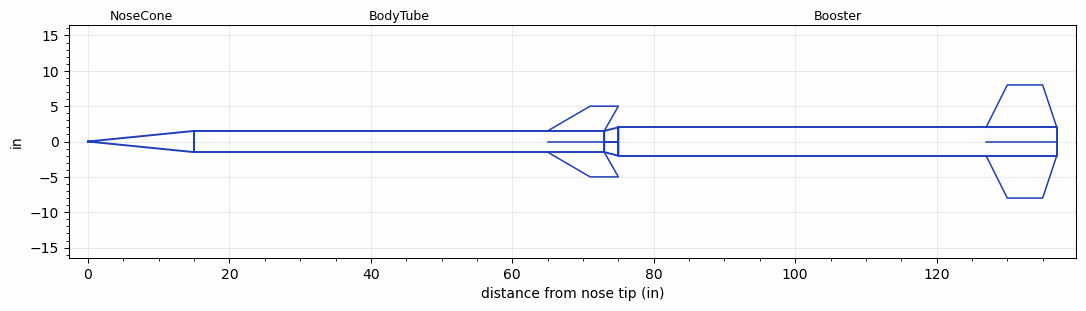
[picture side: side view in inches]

<RASAeroDocument>
 <FileVersion>2</FileVersion>
 <RocketDesign>
  <NoseCone>
   <Length>15</Length>
   <Diameter>3</Diameter>
   <Shape>Conical</Shape>
   <Location>0</Location>
  </NoseCone>
  <BodyTube>
   <Length>58</Length>
   <Diameter>3</Diameter>
   <Location>15</Location>
   <Fin>
    <Count>4</Count>
    <Chord>8</Chord>
    <Span>3.5</Span>
    <SweepDistance>6</SweepDistance>
    <TipChord>4</TipChord>
    <Thickness>0.187</Thickness>
    <LERadius>0.01</LERadius>
    <Location>8</Location>
    <AirfoilSection>Hexagonal</AirfoilSection>
    <FX1>0.75</FX1>
    <FX3>0.75</FX3>
   </Fin>
  </BodyTube>
  <Booster>
   <Length>62</Length>
   <Diameter>4</Diameter>
   <InsideDiameter>3</InsideDiameter>
   <Location>73</Location>
   <ShoulderLength>2</ShoulderLength>
   <Fin>
    <Count>4</Count>
    <Chord>10</Chord>
    <Span>6</Span>
    <SweepDistance>3</SweepDistance>
    <TipChord>5</TipChord>
    <Thickness>0.187</Thickness>
    <LERadius>0.01</LERadius>
    <Location>10</Location>
    <AirfoilSection>Hexagonal</AirfoilSection>
    <FX1>0.75</FX1>
    <FX3>0.75</FX3>
   </Fin>
  </Booster>
  <Surface>Rough Camouflage Paint</Surface>
  <ModifiedBarrowman>True</ModifiedBarrowman>
  <Turbulence>True</Turbulence>
  <UseBooster1>False</UseBooster1>
  <UseBooster2>False</UseBooster2>
 </RocketDesign>
 <LaunchSite>
  <Altitude>3700</Altitude>
  <Pressure>29.92</Pressure>
  <RodAngle>1</RodAngle>
  <RodLength>20</RodLength>
  <Temperature>80</Temperature>
  <WindSpeed>5</WindSpeed>
 </LaunchSite>
 <Recovery>
  <Altitude1>1000</Altitude1>
  <Altitude2>1000</Altitude2>
  <DeviceType1>None</DeviceType1>
  <DeviceType2>None</DeviceType2>
  <Event1>False</Event1>
  <Event2>False</Event2>
  <Size1>1</Size1>
  <Size2>1</Size2>
  <EventType1>None</EventType1>
  <EventType2>None</EventType2>
  <CD1>1.33</CD1>
  <CD2>1.33</CD2>
 </Recovery>
 <SimulationList>
  <Simulation>
   <SustainerEngine>N3992  (TsKrush)</SustainerEngine>
   <SustainerLaunchWt>23.7</SustainerLaunchWt>
   <SustainerCG>47.38</SustainerCG>
   <SustainerIgnitionDelay>10</SustainerIgnitionDelay>
   <Booster1Engine>O7548  (TsKrush)</Booster1Engine>
   <Booster1LaunchWt>57.9</Booster1LaunchWt>
   <Booster1SeparationDelay>0</Booster1SeparationDelay>
   <Booster1IgnitionDelay>0</Booster1IgnitionDelay>
   <Booster1CG>83.53</Booster1CG>
   <IncludeBooster1>True</IncludeBooster1>
   <Booster2Delay>0</Booster2Delay>
   <IncludeBooster2>False</IncludeBooster2>
   <TimetoApogee>173.1559</TimetoApogee>
   <MaxAltitude>439178.2</MaxAltitude>
   <MaxVelocity>5953.627</MaxVelocity>
  </Simulation>
 </SimulationList>
</RASAeroDocument>
